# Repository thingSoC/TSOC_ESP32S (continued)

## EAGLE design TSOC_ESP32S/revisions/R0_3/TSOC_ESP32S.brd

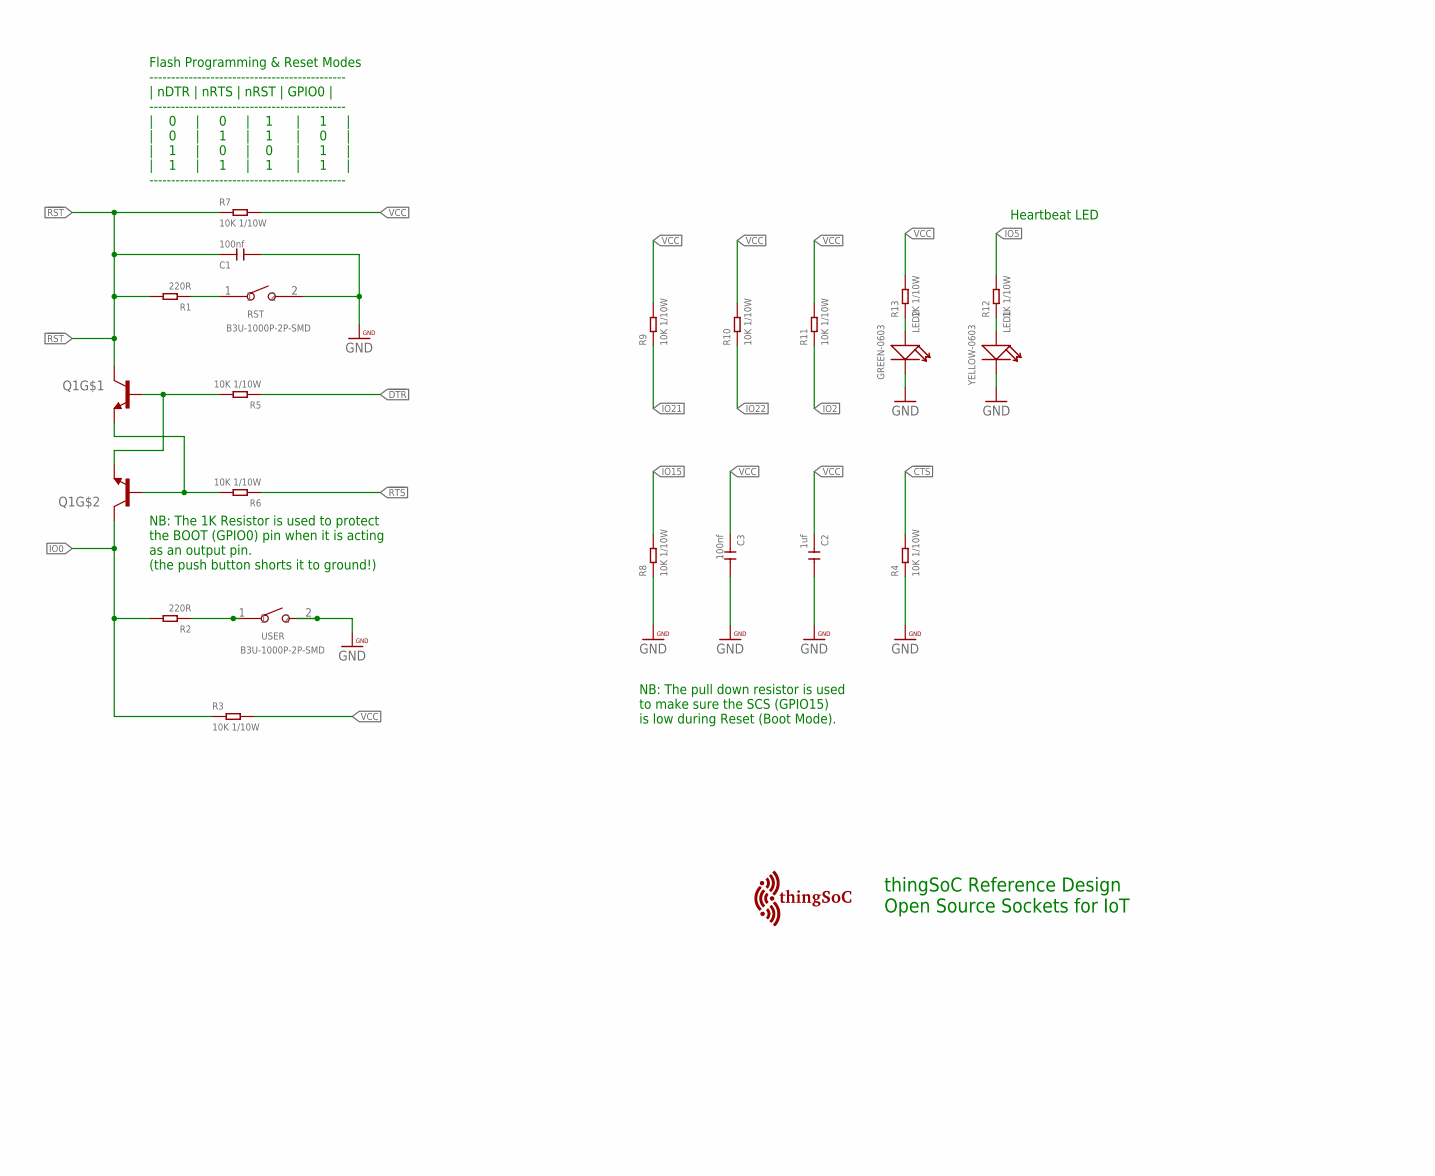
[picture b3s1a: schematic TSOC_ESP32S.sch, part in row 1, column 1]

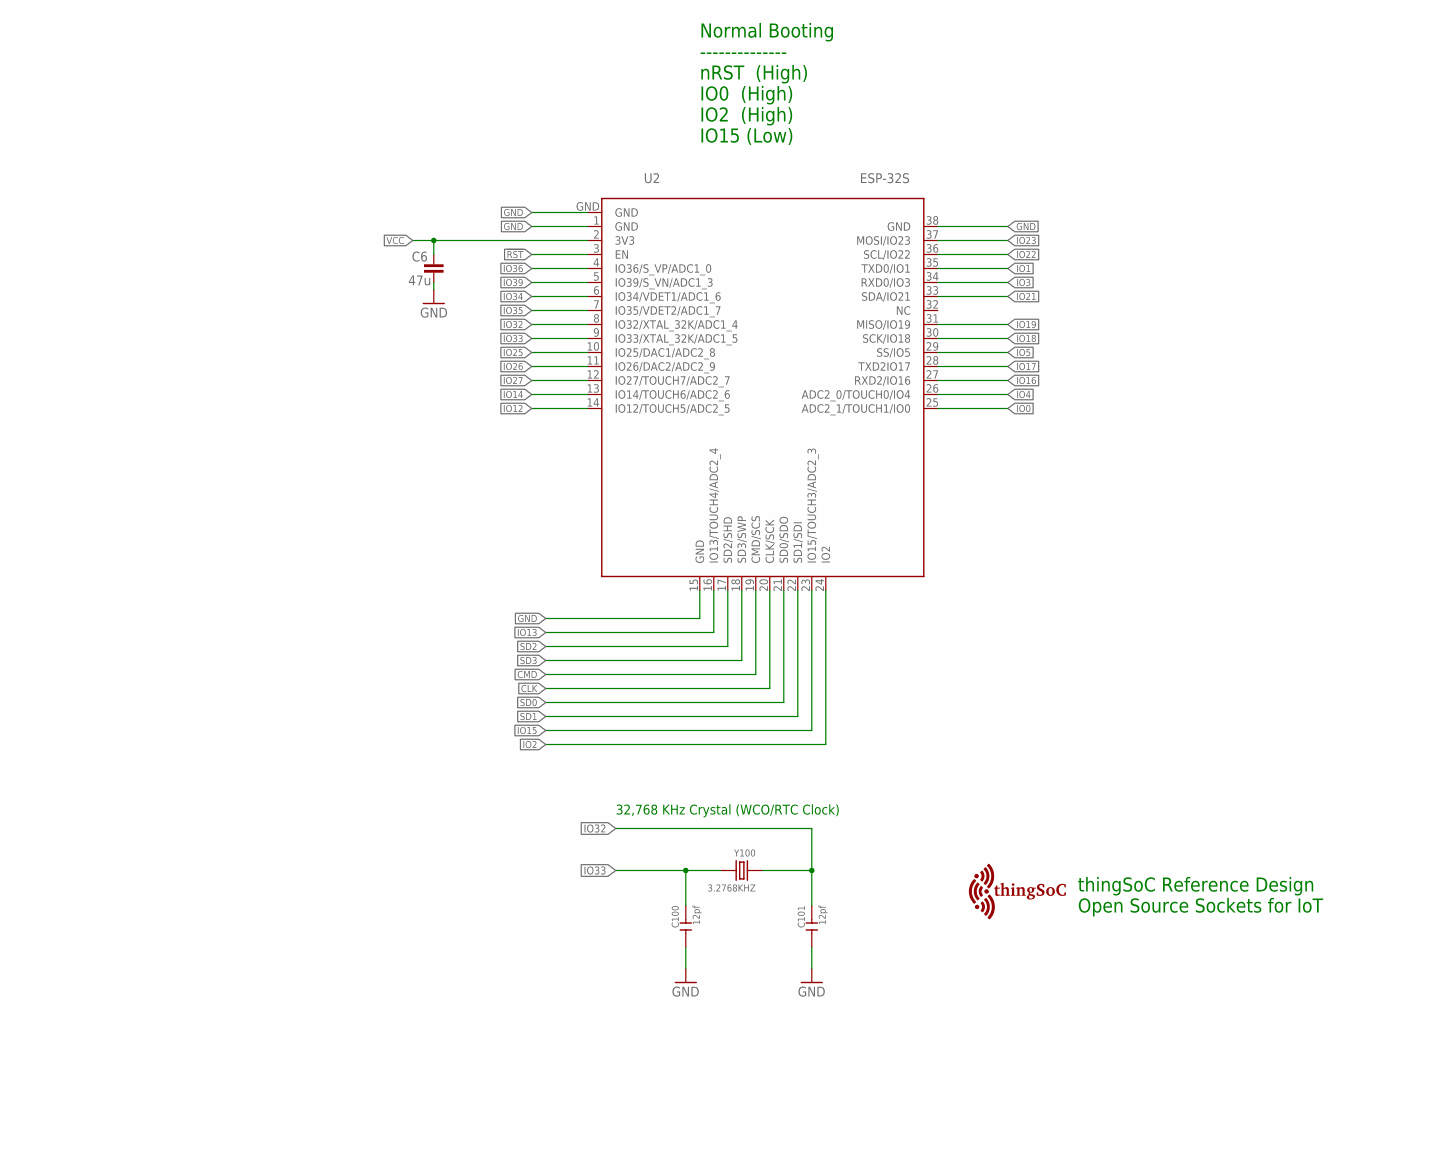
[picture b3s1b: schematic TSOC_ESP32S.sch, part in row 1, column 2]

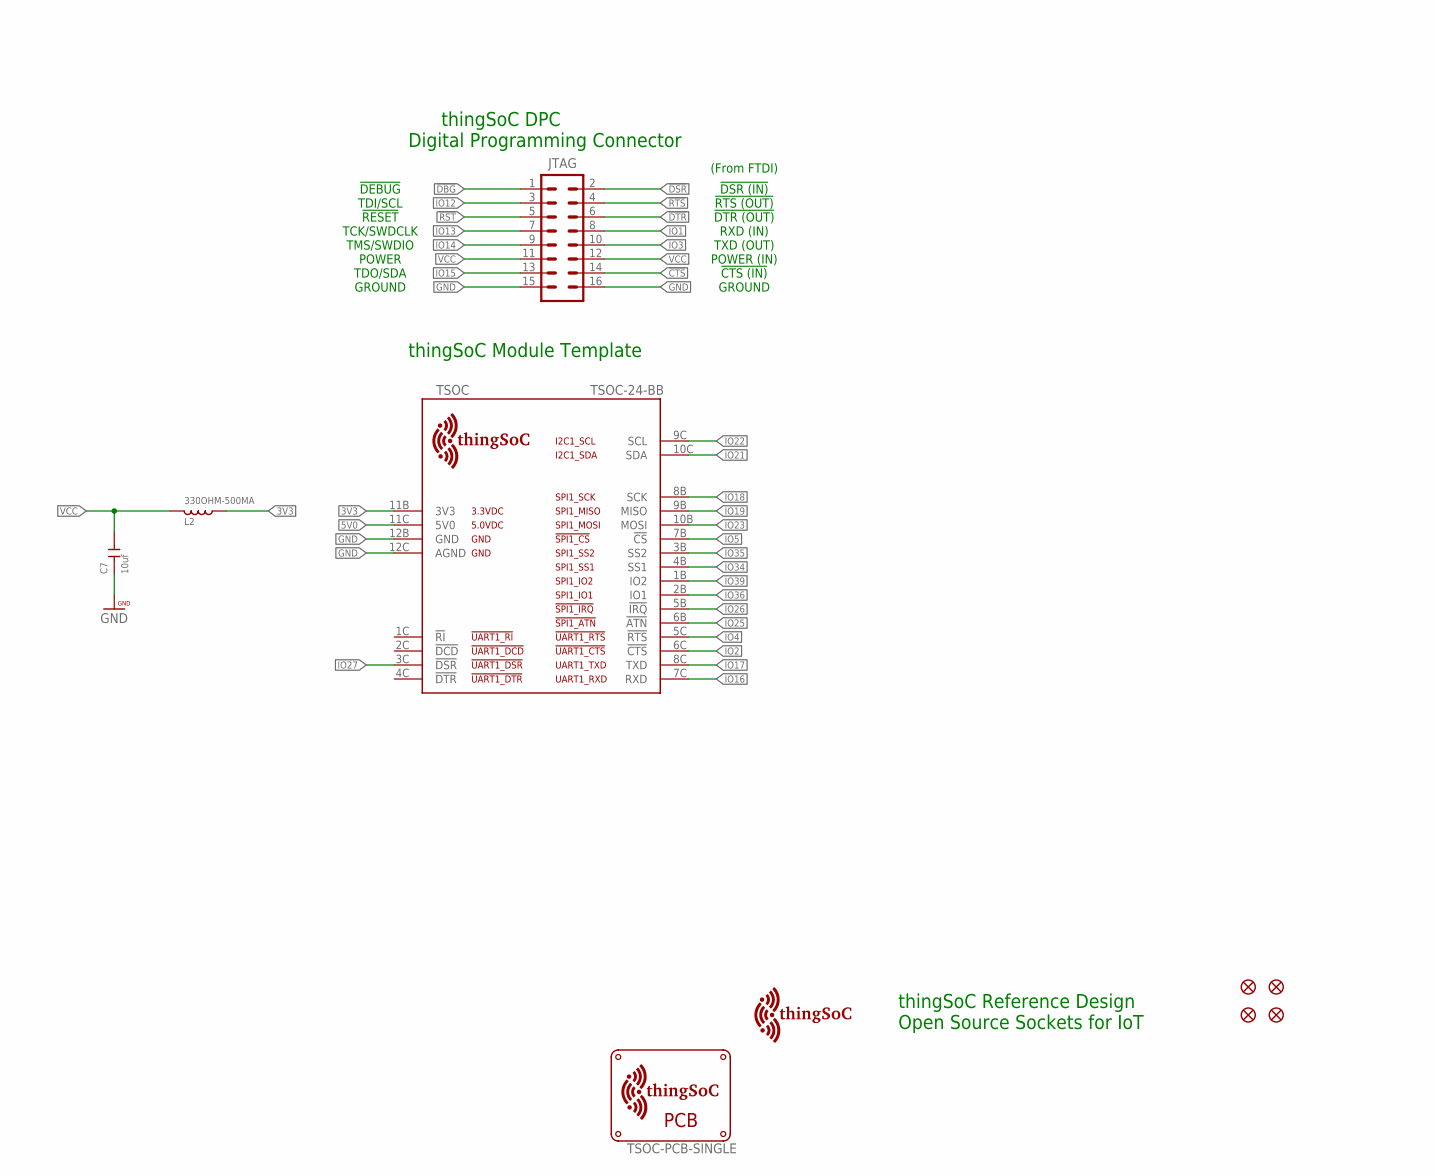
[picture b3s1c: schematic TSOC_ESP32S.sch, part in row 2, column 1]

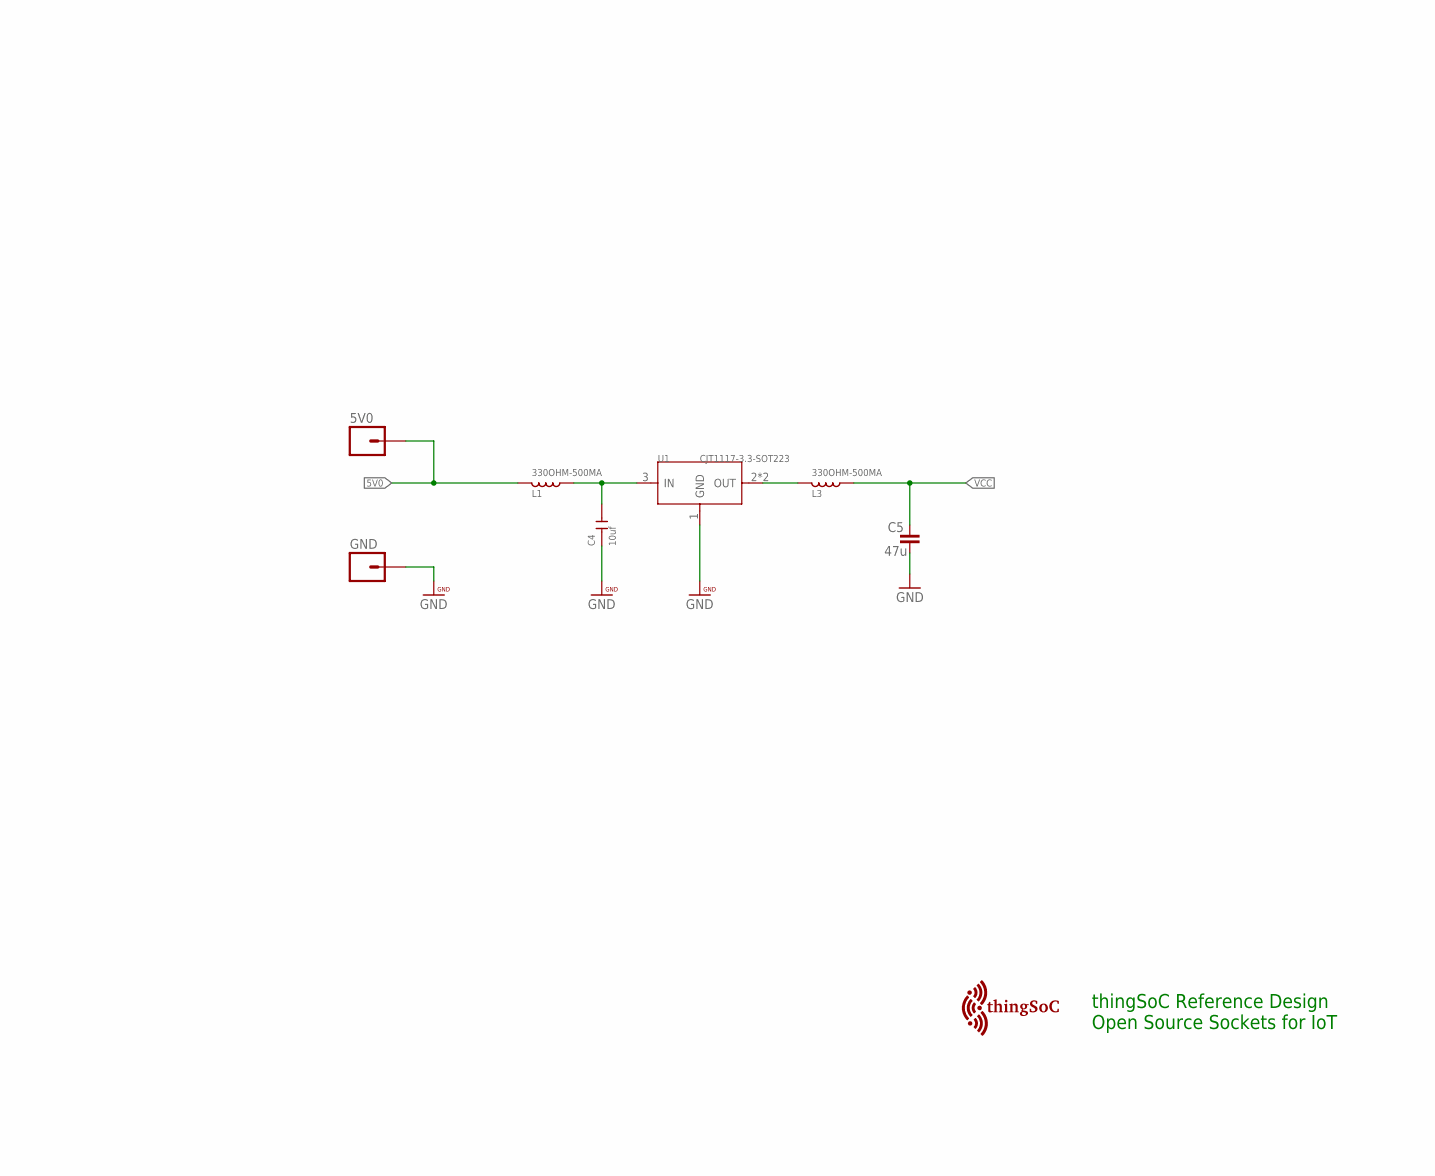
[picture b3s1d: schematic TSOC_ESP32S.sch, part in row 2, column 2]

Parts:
5V0: M01PTH; 1X01
$$U$1, $$U$2: TSOC-LOGO-SMALL; TSOC-LOGO-SML
C1, C3: 100nf; C0603
C2: 1uf; C0603
C4, C7: 10uf; C0603
C5, C6: 47u; C1206
C100, C101: 12pf; C0603
FID1, FID2, FID3, FID4: FIDUCIALUFIDUCIAL; MICRO-FIDUCIAL
GND: M01PTH; 1X01
JTAG: M08X2; 2X8
L1, L2, L3: 330OHM-500MA; L0603
LED1: YELLOW-0603; LED-0603
LED2: GREEN-0603; LED-0603
Q1: MMBT2222A; SOT363
R1, R2: 220R; R0603
R3, R4, R5, R6, R7, R8, R9, R10, R11: 10K 1/10W; R0603
R12, R13: 1K 1/10W; R0603
RST: B3U-1000P-2P-SMD; SW2-2.6-3.0X2.5X1.2+0.4MM
TSOC: TSOC-24-BB; TSOC-BB-S24
U1: CJT1117-3.3-SOT223; SOT-223
U2: ESP-32S
U$1: TSOC-PCB-SINGLE; TSOC-BB-BRD-DIM
U$101: TSOC-LOGO-SMALL; TSOC-LOGO-SML
U$102: TSOC-LOGO-LRG
USER: B3U-1000P-2P-SMD; SW2-2.6-3.0X2.5X1.2+0.4MM
Y100: 3.2768KHZ; X2-SMD-L2.0X1.2X0.55MM

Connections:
3V3: L2.2, TSOC.11B (3V3)
5V: C4.2, L1.2, U1.3 (IN)
5V0: 5V0.1, L1.1, TSOC.11C (5V0)
!CTS: JTAG.14, R4.2
!DBG: JTAG.1
!DSR: JTAG.2
!DTR: JTAG.6, R5.1
!RST: C1.1, JTAG.5, Q1.3 (C), R1.2, R7.1, U2.3 (EN)
!RTS: JTAG.4, R6.1
CLK: U2.20 (CLK/SCK)
CMD: U2.19 (CMD/SCS)
GND: C1.2, C2.2, C3.2, C4.1, C5.1, C6.1, C7.1, C100.2, C101.2, GND.1, JTAG.15, JTAG.16, LED1.-, LED2.-, R4.1, R8.1, RST.2, TSOC.12B (GND), TSOC.12C (AGND), U1.1 (GND), U2.1 (GND), U2.15 (GND), U2.38 (GND), U2.GND, USER.2
IO0: Q1.6 (C), R2.2, R3.1, U2.25 (ADC2_1/TOUCH1/IO0)
IO1: JTAG.8, U2.35 (TXD0/IO1)
IO2: R11.1, TSOC.6C (!CTS), U2.24 (IO2)
IO3: JTAG.10, U2.34 (RXD0/IO3)
IO4: TSOC.5C (!RTS), U2.26 (ADC2_0/TOUCH0/IO4)
IO5: R12.2, TSOC.7B (!CS), U2.29 (SS/IO5)
IO12: JTAG.3, U2.14 (IO12/TOUCH5/ADC2_5)
IO13: JTAG.7, U2.16 (IO13/TOUCH4/ADC2_4)
IO14: JTAG.9, U2.13 (IO14/TOUCH6/ADC2_6)
IO15: JTAG.13, R8.2, U2.23 (IO15/TOUCH3/ADC2_3)
IO16: TSOC.7C (RXD), U2.27 (RXD2/IO16)
IO17: TSOC.8C (TXD), U2.28 (TXD2IO17)
IO18: TSOC.8B (SCK), U2.30 (SCK/IO18)
IO19: TSOC.9B (MISO), U2.31 (MISO/IO19)
IO21: R9.1, TSOC.10C (SDA), U2.33 (SDA/IO21)
IO22: R10.1, TSOC.9C (SCL), U2.36 (SCL/IO22)
IO23: TSOC.10B (MOSI), U2.37 (MOSI/IO23)
IO25: TSOC.6B (!ATN), U2.10 (IO25/DAC1/ADC2_8)
IO26: TSOC.5B (!IRQ), U2.11 (IO26/DAC2/ADC2_9)
IO27: TSOC.3C (!DSR), U2.12 (IO27/TOUCH7/ADC2_7)
IO32: C101.1, U2.8 (IO32/XTAL_32K/ADC1_4), Y100.1
IO33: C100.1, U2.9 (IO33/XTAL_32K/ADC1_5), Y100.2
IO34: TSOC.4B (SS1), U2.6 (IO34/VDET1/ADC1_6)
IO35: TSOC.3B (SS2), U2.7 (IO35/VDET2/ADC1_7)
IO36: TSOC.2B (IO1), U2.4 (IO36/S_VP/ADC1_0)
IO39: TSOC.1B (IO2), U2.5 (IO39/S_VN/ADC1_3)
unnamed: LED1.+, R12.1
unnamed: R2.1, USER.1
unnamed: R1.1, RST.1
unnamed: L3.1, U1.2 (OUT), U1.TER (OUT)
unnamed: LED2.+, R13.1
RES: Q1.1 (E), Q1.5 (B), R5.2
ROS: Q1.2 (B), Q1.4 (E), R6.2
SD0: U2.21 (SD0/SDO)
SD1: U2.22 (SD1/SDI)
SD2: U2.17 (SD2/SHD)
SD3: U2.18 (SD3/SWP)
VCC: C2.1, C3.1, C5.2, C6.2, C7.2, JTAG.11, JTAG.12, L2.1, L3.2, R3.2, R7.2, R9.2, R10.2, R11.2, R13.2, U2.2 (3V3)

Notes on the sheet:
Heartbeat LED
thingSoC Reference Design Open Source Sockets for IoT
TDO/SDA
TDI/SCL
!RESET
TCK/SWDCLK
TMS/SWDIO
POWER
GROUND
!DEBUG
!DSR (IN)
!RTS (OUT)
!CTS (IN)
!DTR (OUT)
TXD (OUT)
RXD (IN)
POWER (IN)
thingSoC DPC Digital Programming Connector
Normal Booting -------------- nRST (High) IO0 (High) IO2 (High) IO15 (Low)
thingSoC Module Template
Flash Programming & Reset Modes --------------------------------------------- | nDTR | nRTS | nRST | GPIO0 | --------------------------------------------- | 0 | 0 | 1 | 1 | | 0 | 1 | 1 | 0 | | 1 | 0 | 0 | 1 | | 1 | 1 | 1 | 1 | ---------------------------------------------
NB: The 1K Resistor is used to protect the BOOT (GPIO0) pin when it is acting as an output pin. (the push button shorts it to ground!)
NB: The pull down resistor is used to make sure the SCS (GPIO15) is low during Reset (Boot Mode).
(From FTDI)
32,768 KHz Crystal (WCO/RTC Clock)

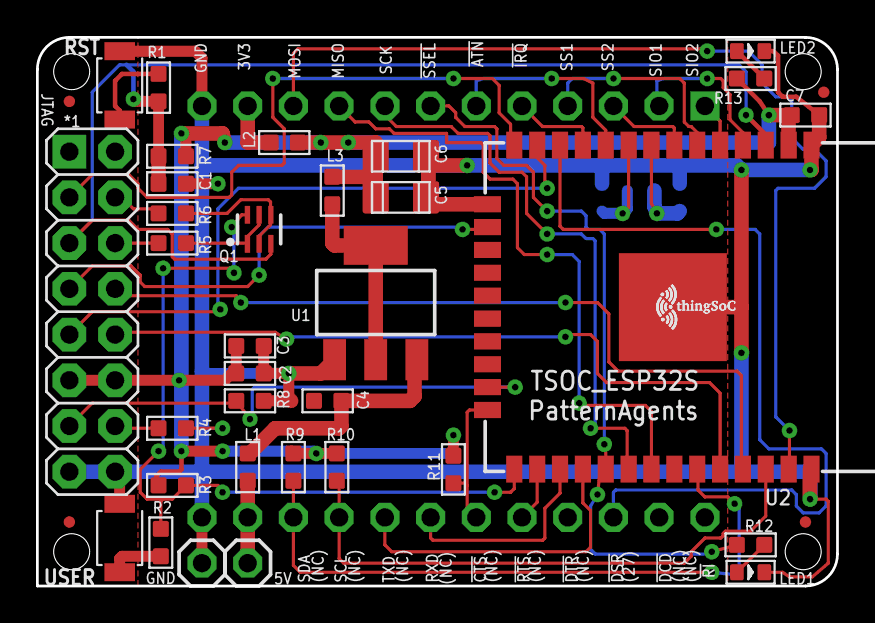
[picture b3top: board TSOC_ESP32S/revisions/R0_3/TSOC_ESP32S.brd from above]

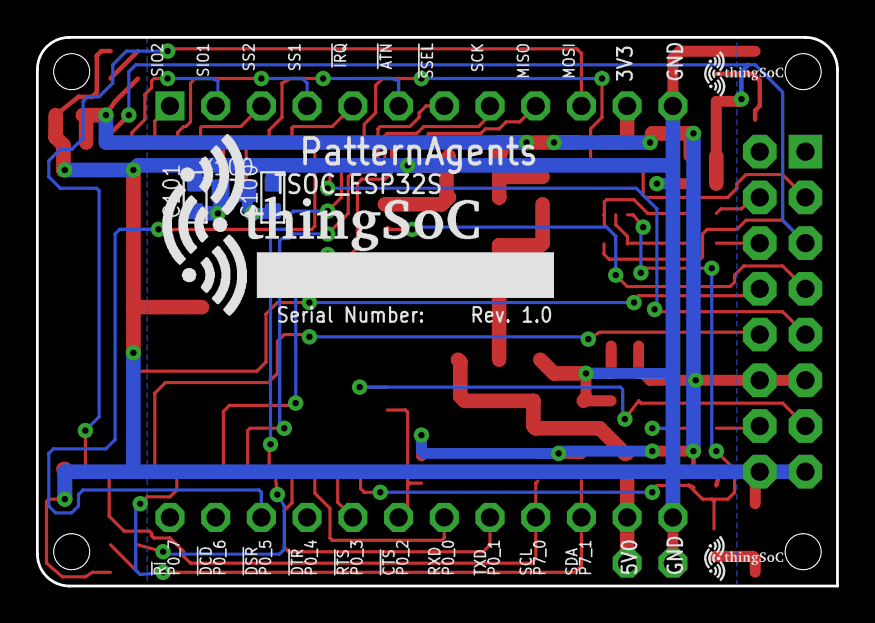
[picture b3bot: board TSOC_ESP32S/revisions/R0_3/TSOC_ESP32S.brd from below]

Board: 2 copper layers, 44.5 x 30.5 mm, 47 parts (6 on the bottom side), 42 nets.

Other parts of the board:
U$100: TSOC-LOGO-SMALL; TSOC-LOGO-SML

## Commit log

2017-01-14 update documetation
2017-02-12 update arduino/blynk example
2017-02-28 update docs
2019-02-14 update images
2019-02-20 2019 update
